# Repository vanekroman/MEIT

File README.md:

# Modular system for Electrical Impedance Tomography

Hardware, Firmware and Software development.

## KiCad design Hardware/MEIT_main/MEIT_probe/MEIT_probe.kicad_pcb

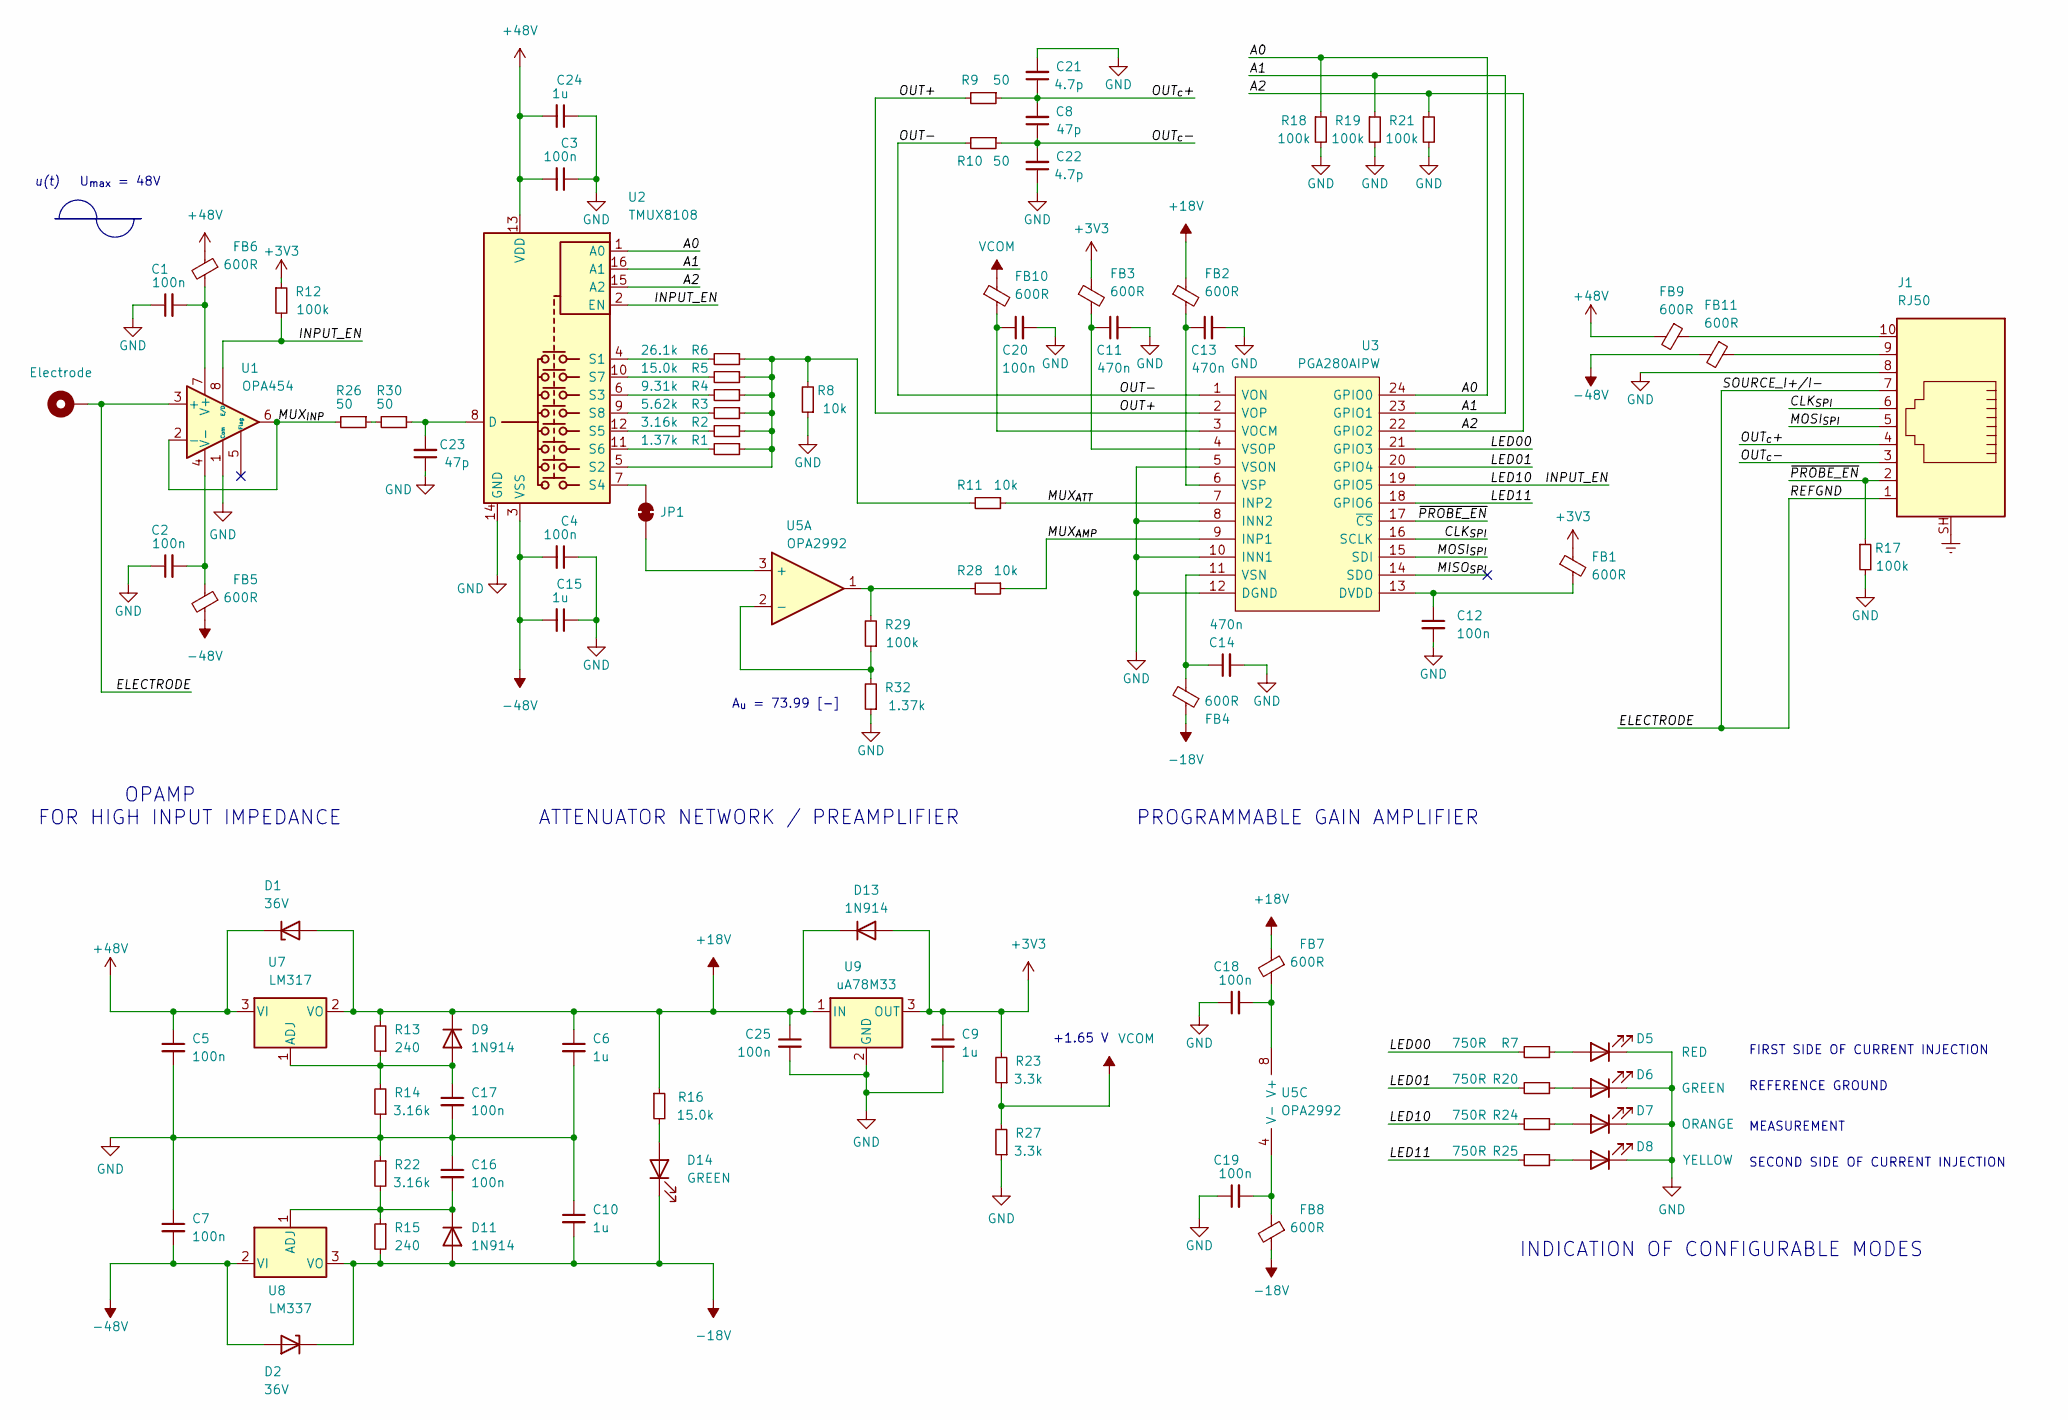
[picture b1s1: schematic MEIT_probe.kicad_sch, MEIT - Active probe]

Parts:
C1, C2, C3, C4, C5, C7, C12, C16, C17, C18, C19, C20, C25: 100n; C_0805_2012Metric_Pad1.18x1.45mm_HandSolder; Part Number 100n
C6, C9, C10, C15, C24: 1u; C_0805_2012Metric_Pad1.18x1.45mm_HandSolder; Part Number 1u
C8, C23: 47p; C_0805_2012Metric_Pad1.18x1.45mm_HandSolder; Part Number 100n
C11, C13, C14: 470n; C_0805_2012Metric_Pad1.18x1.45mm_HandSolder; Part Number 470n
C21, C22: 4.7p; C_0805_2012Metric_Pad1.18x1.45mm_HandSolder; Part Number 100n
D1, D2: 36V; D_SMB_403A; Part Number 36V
D5: RED; LED_0603_1608Metric_Pad1.05x0.95mm_HandSolder; Part Number CSL1901UW1
D6, D14: GREEN; LED_0603_1608Metric_Pad1.05x0.95mm_HandSolder; Part Number CSL1901MW1
D7: ORANGE; LED_0603_1608Metric_Pad1.05x0.95mm_HandSolder; Part Number CSL1901DW1
D8: YELLOW; LED_0603_1608Metric_Pad1.05x0.95mm_HandSolder; Part Number CSL1901YW1
D9, D11, D13: 1N914; D_SOD-523F; Part Number 1N914WT
FB1, FB2, FB3, FB4, FB5, FB6, FB7, FB8, FB9, FB10, FB11: 600R; LED_0603_1608Metric_Pad1.05x0.95mm_HandSolder; Part Number FBMH1608HM601
H1: Electrode
J1: RJ50; RJ50_117345801; Part Number RJE051AA1310
JP1: SEL_CAP; SolderJumper-2_P1.3mm_Bridged_Pad1.0x1.5mm
R1: 1.37k; R_0805_2012Metric_Pad1.20x1.40mm_HandSolder; Part Number 1.37k
R2, R14, R22: 3.16k; R_0805_2012Metric_Pad1.20x1.40mm_HandSolder; Part Number 3.16k
R3: 5.62k; R_0805_2012Metric_Pad1.20x1.40mm_HandSolder; Part Number 5.62k
R4: 9.31k; R_0805_2012Metric_Pad1.20x1.40mm_HandSolder; Part Number 9.31k
R5, R16: 15.0k; R_0805_2012Metric_Pad1.20x1.40mm_HandSolder; Part Number 15.0k
R6: 26.1k; R_0805_2012Metric_Pad1.20x1.40mm_HandSolder; Part Number 26.1k
R7, R20, R24, R25: 750R; R_0805_2012Metric_Pad1.20x1.40mm_HandSolder; Part Number 750R
R8: 10k; R_0805_2012Metric_Pad1.20x1.40mm_HandSolder; Part Number 10k
R9, R10, R26, R30: 50; R_0805_2012Metric_Pad1.20x1.40mm_HandSolder; Part Number 100k
R11, R28: 10k; R_0805_2012Metric_Pad1.20x1.40mm_HandSolder; Part Number 3.16k
R12, R29: 100k; R_0805_2012Metric_Pad1.20x1.40mm_HandSolder; Part Number 240
R13, R15: 240; R_0805_2012Metric_Pad1.20x1.40mm_HandSolder; Part Number 240
R17, R18, R19, R21: 100k; R_0805_2012Metric_Pad1.20x1.40mm_HandSolder; Part Number 100k
R23, R27: 3.3k; R_0805_2012Metric_Pad1.20x1.40mm_HandSolder; Part Number 3.3k
R32: 1.37k; R_0805_2012Metric_Pad1.20x1.40mm_HandSolder; Part Number 3.16k
U1: OPA454; SOIC-8-1EP_3.9x4.9mm_P1.27mm_EP2.514x3.2mm; Part Number OPA454AIDDA
U2: TMUX8108; TSSOP-16_4.4x5mm_P0.65mm; Part Number TMUX8108PWR
U3: PGA280AIPW; SOP65P640X120-24N; Manufacturer_Part_Number PGA280AIPW; Mouser Part Number 595-PGA280AIPW
U5: OPA2992; SOIC-8_3.9x4.9mm_P1.27mm; MPN OPA2992IDR
U7: LM317; SOT-223-3_TabPin2; MPN LM317MDCYR
U8: LM337; SOT-223-3_TabPin2; MPN LM337IMP/NOPB
U9: uA78M33; SOT-223-3_TabPin2; MPN UA78M33QDCYRG4Q1

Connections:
+3V3: C9.1, D13.2 (A), FB1.1, FB3.1, R12.1, R23.2, U9.3 (OUT)
+18V: C6.1, C25.1, D1.2 (A), D9.1 (K), D13.1 (K), FB2.1, FB7.1, R13.2, R16.1, U7.2 (VO), U9.1 (IN)
+48V: C3.2, C5.1, C24.2, D1.1 (K), FB6.1, FB9.1, FB9.2, J1.10, U2.13 (VDD), U7.3 (VI)
-18V: C10.2, D2.1 (K), D11.2 (A), D14.1 (K), FB4.1, FB8.2, R15.2, U8.3 (VO)
-48V: C4.2, C7.2, C15.2, D2.2 (A), FB5.2, FB11.1, FB11.2, J1.9, U2.3 (VSS), U8.2 (VI)
/A0: R18.1, U2.1 (A0), U3.24 (GPIO0)
/A1: R19.1, U2.16 (A1), U3.23 (GPIO1)
/A2: R21.1, U2.15 (A2), U3.22 (GPIO2)
/CLK_{SPI}: J1.6, U3.16 (SCLK); also elsewhere on the board
/ELECTRODE: H1.1, J1.1, J1.7, U1.3 (+); also elsewhere on the board
/INPUT_EN: R12.2, R24.2, U1.8 (E/D), U2.2 (EN), U3.19 (GPIO5)
/LED00: R7.2, U3.21 (GPIO3)
/LED01: R20.2, U3.20 (GPIO4)
/LED11: R25.2, U3.18 (GPIO6)
/MISO_{SPI}: U3.14 (SDO)
/MOSI_{SPI}: J1.5, U3.15 (SDI); also elsewhere on the board
/MUX_{AMP}: R28.1, U3.9 (INP1)
/MUX_{ATT}: R11.1, U3.7 (INP2)
/MUX_{INP}: R26.2, U1.2 (-), U1.6
/OUT+: R9.2, U3.2 (VOP)
/OUT-: R10.2, U3.1 (VON)
/OUT_{c}+: C8.2, C21.1, J1.4, R9.1
/OUT_{c}-: C8.1, C22.2, J1.3, R10.1
/~PROBE_EN: J1.2, R17.1, U3.17 (~CS)
Earth: J1.SH
GND: C1.1, C2.1, C3.1, C4.1, C5.2, C6.2, C7.1, C9.2, C10.1, C11.2, C12.2, C13.2, C14.2, C15.1, C16.1, C17.2, C18.1, C19.1, C20.2, C21.2, C22.1, C23.1, C24.1, C25.2, D5.1 (K), D6.1 (K), D7.1 (K), D8.1 (K), J1.8, R8.1, R14.1, R17.2, R18.2, R19.2, R21.2, R22.1, R27.1, R32.1, U1.1 (Com), U2.14 (GND), U3.5 (VSON), U3.8 (INN2), U3.10 (INN1), U3.12 (DGND), U9.2 (GND)
unnamed: D5.2 (A), R7.1
unnamed: D6.2 (A), R20.1
unnamed: D7.2 (A), R24.1
unnamed: D8.2 (A), R25.1
unnamed: C17.1, D9.2 (A), R13.1, R14.2, U7.1 (ADJ)
unnamed: C16.2, D11.1 (K), R15.1, R22.2, U8.1 (ADJ)
unnamed: D14.2 (A), R16.2
unnamed: JP1.1 (A), U2.7 (S4)
unnamed: JP1.2 (B), U5.3 (+)
unnamed: R26.1, R30.2
unnamed: R28.2, R29.2, U5.1
unnamed: C1.2, FB6.2, U1.7 (V+)
unnamed: C2.2, FB5.1, U1.4 (V-)
unnamed: C23.2, R30.1, U2.8 (D)
unnamed: R6.2, U2.4 (S1)
unnamed: R1.1, R2.1, R3.1, R4.1, R5.1, R6.1, R8.2, R11.2, U2.5 (S2)
unnamed: R4.2, U2.6 (S3)
unnamed: R2.2, U2.12 (S5)
unnamed: R1.2, U2.11 (S6)
unnamed: R5.2, U2.10 (S7)
unnamed: R3.2, U2.9 (S8)
unnamed: C12.1, FB1.2, U3.13 (DVDD)
unnamed: C20.1, FB10.2, U3.3 (VOCM)
unnamed: C14.1, FB4.2, U3.11 (VSN)
unnamed: C11.1, FB3.2, U3.4 (VSOP)
unnamed: C13.1, FB2.2, U3.6 (VSP)
unnamed: R29.1, R32.2, U5.2 (-)
unnamed: C18.2, FB7.2, U5.8 (V+)
unnamed: C19.2, FB8.1, U5.4 (V-)
VCOM: FB10.1, R23.1, R27.2

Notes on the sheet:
A_{u} = 73.99 [-]
FIRST SIDE OF CURRENT INJECTION
U_{max} = 48V
+1.65 V
OPAMP FOR HIGH INPUT IMPEDANCE
MEASUREMENT
REFERENCE GROUND
INDICATION OF CONFIGURABLE MODES
ATTENUATOR NETWORK / PREAMPLIFIER
SECOND SIDE OF CURRENT INJECTION
PROGRAMMABLE GAIN AMPLIFIER
u(t)

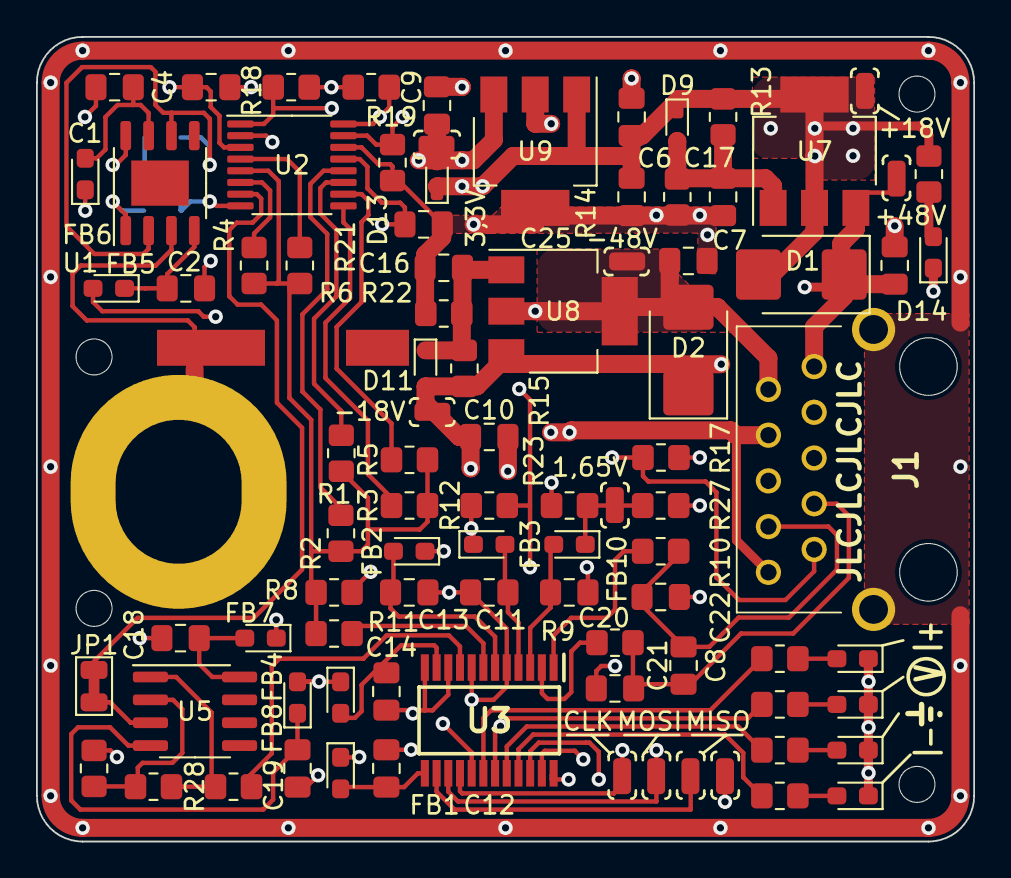
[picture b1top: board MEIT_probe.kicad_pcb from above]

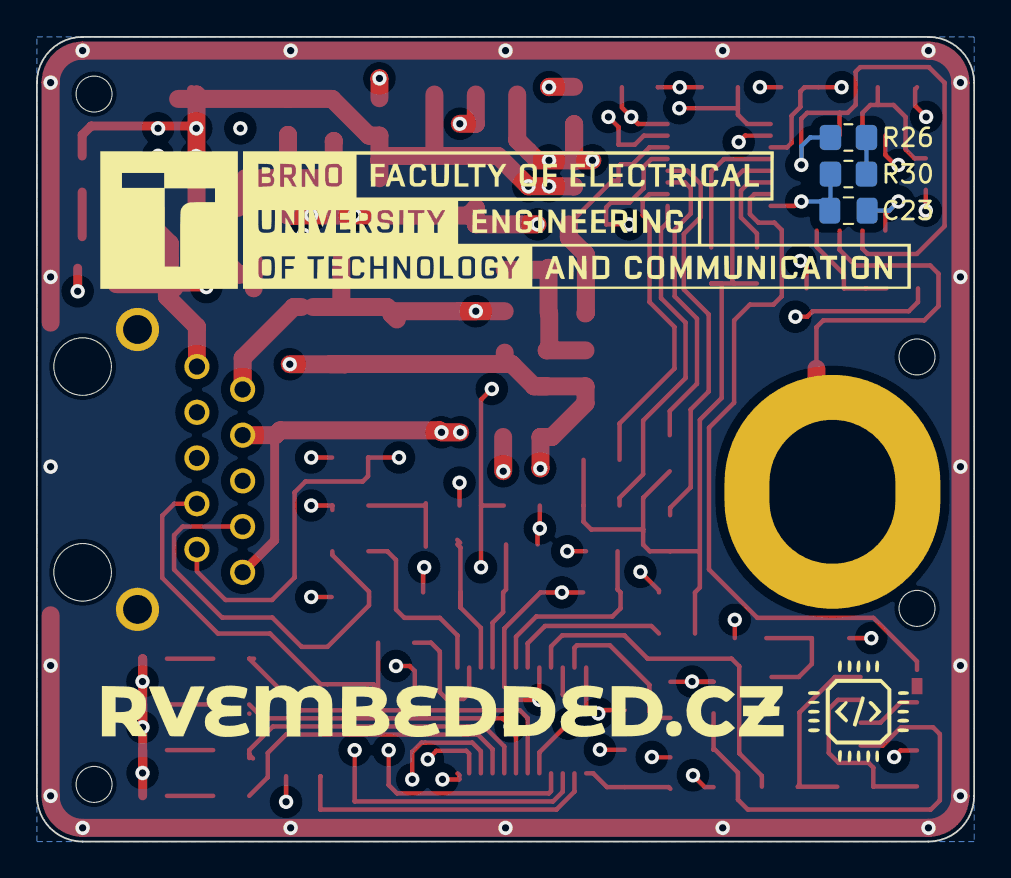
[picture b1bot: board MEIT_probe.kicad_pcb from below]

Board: 4 copper layers, 52.1 x 44.7 mm, 87 parts (3 on the bottom side), 54 nets.

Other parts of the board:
CLK: SolderWirePad_1x01_SMD_1x2mm
J**: 2060451998404
MISO: SolderWirePad_1x01_SMD_1x2mm
MISO#2: SolderWirePad_1x01_SMD_1x2mm
MOSI: SolderWirePad_1x01_SMD_1x2mm

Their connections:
/CLK_{SPI}: CLK.1; also elsewhere on the board
/ELECTRODE: J**.1; also elsewhere on the board
/MOSI_{SPI}: MOSI.1; also elsewhere on the board

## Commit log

2024-10-14 Initial commit
    Firmware, Hardware and Software as it is on dspace.vut.cz
2024-10-15 C lang gitignore add
2024-10-17 build directory gitignore add
2024-10-17 Drivers directory gitignore add
2024-10-17 not building local sysmem and syscalls
    Comment sysmem.c and syscalls.c files, causes ld error if not commented
2024-10-17 new build
    setting up new osx enviroment + new CubeMX version
2024-10-18 gitignore reorganization
    gitignore reorganization
2024-10-21 gitignore update
    OSx specific files added
2024-10-21 gitignore delete independent keyword
2024-10-21 gitignore reorganization to subfolders
